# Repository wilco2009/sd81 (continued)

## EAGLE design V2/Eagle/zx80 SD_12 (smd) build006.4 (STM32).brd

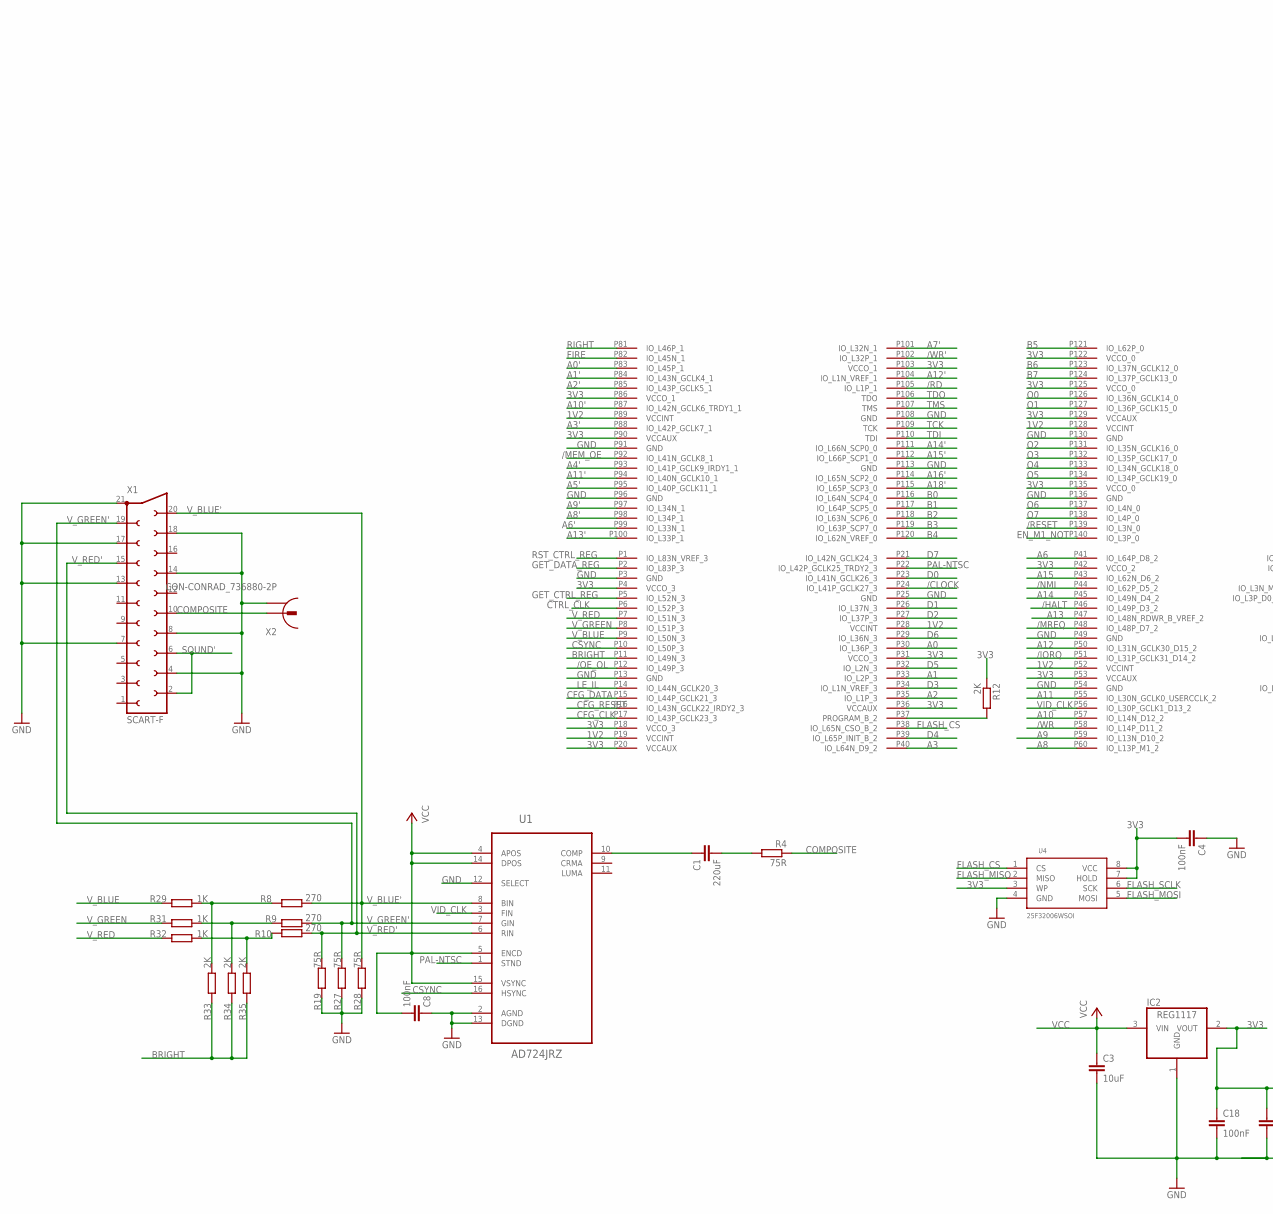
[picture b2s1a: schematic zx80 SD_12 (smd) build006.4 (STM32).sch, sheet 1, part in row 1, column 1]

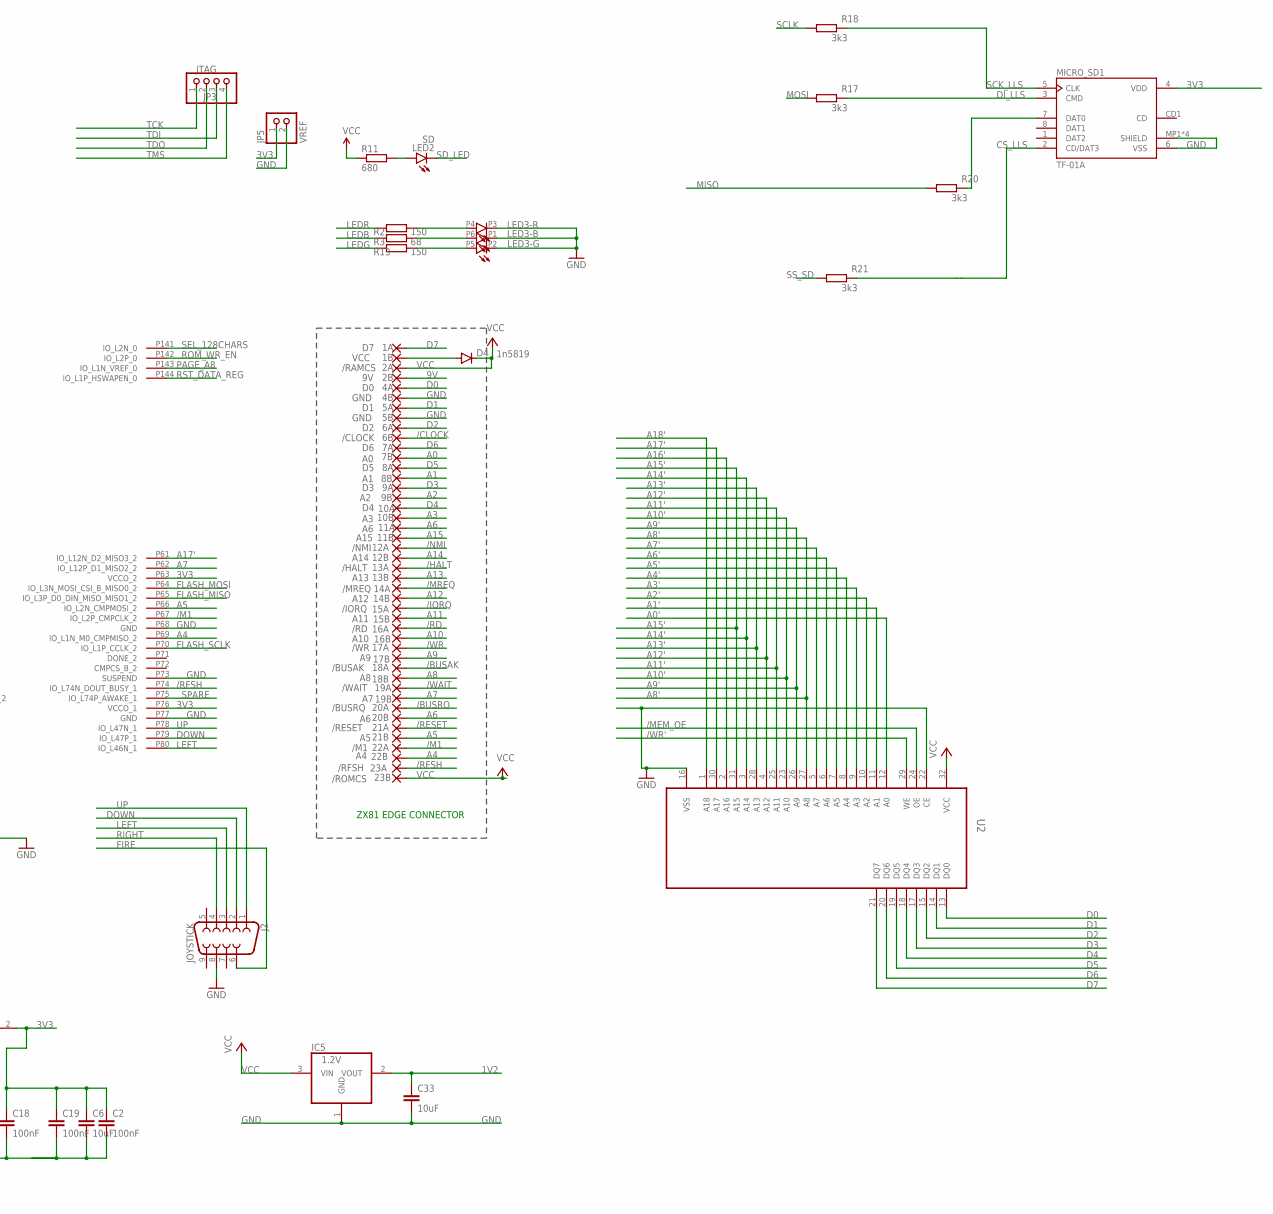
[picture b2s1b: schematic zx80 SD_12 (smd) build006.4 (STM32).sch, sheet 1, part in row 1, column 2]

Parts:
1A: D7; EDGEPIN
1B: VCC; EDGEPIN
2A: /RAMCS; EDGEPIN
2B: 9V; EDGEPIN
4A: D0; EDGEPIN
4B, 5B: GND; EDGEPIN
5A: D1; EDGEPIN
6A: D2; EDGEPIN
6B: /CLOCK; EDGEPIN
7A: D6; EDGEPIN
7B: A0; EDGEPIN
8A: D5; EDGEPIN
8B: A1; EDGEPIN
9A: D3; EDGEPIN
9B: A2; EDGEPIN
10A: D4; EDGEPIN
10B: A3; EDGEPIN
11A, 20B: A6; EDGEPIN
11B: A15; EDGEPIN
12A: /NMI; EDGEPIN
12B: A14; EDGEPIN
13A: /HALT; EDGEPIN
13B: A13; EDGEPIN
14A: /MREQ; EDGEPIN
14B: A12; EDGEPIN
15A: /IORQ; EDGEPIN
15B: A11; EDGEPIN
16A: /RD; EDGEPIN
16B: A10; EDGEPIN
17A: /WR; EDGEPIN
17B: A9; EDGEPIN
18A: /BUSAK; EDGEPIN
18B: A8; EDGEPIN
19A: /WAIT; EDGEPIN
19B: A7; EDGEPIN
20A: /BUSRQ; EDGEPIN
21A: /RESET; EDGEPIN
21B: A5; EDGEPIN
22A: /M1; EDGEPIN
22B: A4; EDGEPIN
23A: /RFSH; EDGEPIN
23B: /ROMCS; EDGEPIN
C1: 220uF; C0603K
C2, C4, C18, C19: 100nF; C0603
C3, C6, C33: 10uF; C0603
C8: 100nF; C0603K
D4: 1n5819; SOD323-W
IC2: REG1117; SOT223
IC5: 1.2V; SOT223
J2: JOYSTICK; DB9_MALE
JP3: JTAG; 1X04
JP5: VREF; 1X02
LED2: SD; CHIPLED_0805
LED3: STATUS; 3535-PLCC6
MICRO_SD1: TF-01A
R2, R13: 150; R0603
R3: 68; R0603
R4: 75R; R0603
R8, R9, R10: 270; R0402
R11: 680; R0603
R12: 2K; R0603
R17, R18, R20, R21: 3k3; R0603
R19, R27, R28: 75R; R0402
R29, R31, R32: 1K; R0402
R33, R34, R35: 2K; R0402
U1: AD724JRZ; SOIC127P1032X265-16N
U2: AS6C4008; SOP32-5
U4: 25F32006WSOI; SO08-EIAJ
U$1: XC6SLX9-2TQG144C; TQ144
X1: SCART-F
X2: CON-CONRAD_736880-2P; 3P

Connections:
1V2: C33.1, IC5.2 (VOUT), U$1.P19 (VCCINT), U$1.P28 (VCCINT), U$1.P52 (VCCINT), U$1.P89 (VCCINT), U$1.P128 (VCCINT)
3V3: C2.1, C4.2, C6.1, C18.1, C19.1, IC2.2 (VOUT), JP5.1, MICRO_SD1.4 (VDD), R12.1, U4.3 (WP), U4.7 (HOLD), U4.8 (VCC), U$1.P4 (VCCO_3), U$1.P18 (VCCO_3), U$1.P20 (VCCAUX), U$1.P31 (VCCO_3), U$1.P36 (VCCAUX), U$1.P42 (VCCO_2), U$1.P53 (VCCAUX), U$1.P63 (VCCO_2), U$1.P76 (VCCO_1), U$1.P86 (VCCO_1), U$1.P90 (VCCAUX), U$1.P103 (VCCO_1), U$1.P122 (VCCO_0), U$1.P125 (VCCO_0), U$1.P129 (VCCAUX), U$1.P135 (VCCO_0); also elsewhere on the board
9V: 2B.1
/BUSAK: 18A.1
/BUSRQ: 20A.1
/CLOCK: 6B.1, U$1.P24 (IO_L41P_GCLK27_3)
/HALT: 13A.1, U$1.P46 (IO_L49P_D3_2)
/IORQ: 15A.1, U$1.P51 (IO_L31P_GCLK31_D14_2)
/M1: 22A.1, U$1.P67 (IO_L2P_CMPCLK_2)
/MEM_OE: U2.24 (OE), U$1.P92 (IO_L41N_GCLK8_1)
/MREQ: 14A.1, U$1.P48 (IO_L48P_D7_2)
/NMI: 12A.1, U$1.P44 (IO_L62P_D5_2)
/OE_OL: U$1.P12 (IO_L49P_3); also elsewhere on the board
/RD: 16A.1, U$1.P105 (IO_L1P_1)
/RESET: 21A.1, U$1.P139 (IO_L3N_0); also elsewhere on the board
/RFSH: 23A.1, U$1.P74 (IO_L74N_DOUT_BUSY_1)
/WAIT: 19A.1; also elsewhere on the board
/WR: 17A.1, U$1.P58 (IO_L14P_D11_2)
/WR': U2.29 (WE), U$1.P102 (IO_L32P_1); also elsewhere on the board
A0: 7B.1, U$1.P30 (IO_L36P_3)
A0': U2.12 (A0), U$1.P83 (IO_L45P_1); also elsewhere on the board
A1: 8B.1, U$1.P33 (IO_L2P_3)
A1': U2.11 (A1), U$1.P84 (IO_L43N_GCLK4_1); also elsewhere on the board
A2: 9B.1, U$1.P35 (IO_L1P_3)
A2': U2.10 (A2), U$1.P85 (IO_L43P_GCLK5_1); also elsewhere on the board
A3: 10B.1, U$1.P40 (IO_L64N_D9_2)
A3': U2.9 (A3), U$1.P88 (IO_L42P_GCLK7_1); also elsewhere on the board
A4: 22B.1, U$1.P69 (IO_L1N_M0_CMPMISO_2)
A4': U2.8 (A4), U$1.P93 (IO_L41P_GCLK9_IRDY1_1); also elsewhere on the board
A5: 21B.1, U$1.P66 (IO_L2N_CMPMOSI_2)
A5': U2.7 (A5), U$1.P95 (IO_L40P_GCLK11_1); also elsewhere on the board
A6: 11A.1, 20B.1, U$1.P41 (IO_L64P_D8_2)
A6': U2.6 (A6), U$1.P99 (IO_L33N_1); also elsewhere on the board
A7: 19B.1, U$1.P62 (IO_L12P_D1_MISO2_2)
A7': U2.5 (A7), U$1.P101 (IO_L32N_1); also elsewhere on the board
A8: 18B.1, U$1.P60 (IO_L13P_M1_2)
A8': U2.27 (A8), U$1.P98 (IO_L34P_1); also elsewhere on the board
A9: 17B.1, U$1.P59 (IO_L13N_D10_2)
A9': U2.26 (A9), U$1.P97 (IO_L34N_1); also elsewhere on the board
A10: 16B.1, U$1.P57 (IO_L14N_D12_2)
A10': U2.23 (A10), U$1.P87 (IO_L42N_GCLK6_TRDY1_1); also elsewhere on the board
A11: 15B.1, U$1.P55 (IO_L30N_GCLK0_USERCCLK_2)
A11': U2.25 (A11), U$1.P94 (IO_L40N_GCLK10_1); also elsewhere on the board
A12: 14B.1, U$1.P50 (IO_L31N_GCLK30_D15_2)
A12': U2.4 (A12), U$1.P104 (IO_L1N_VREF_1); also elsewhere on the board
A13: 13B.1, U$1.P47 (IO_L48N_RDWR_B_VREF_2)
A13': U2.28 (A13), U$1.P100 (IO_L33P_1); also elsewhere on the board
A14: 12B.1, U$1.P45 (IO_L49N_D4_2)
A14': U2.3 (A14), U$1.P111 (IO_L66N_SCP0_0); also elsewhere on the board
A15: 11B.1, U$1.P43 (IO_L62N_D6_2)
A15': U2.31 (A15), U$1.P112 (IO_L66P_SCP1_0); also elsewhere on the board
A16': U2.2 (A16), U$1.P114 (IO_L65N_SCP2_0); also elsewhere on the board
A17': U2.30 (A17), U$1.P61 (IO_L12N_D2_MISO3_2); also elsewhere on the board
A18': U2.1 (A18), U$1.P115 (IO_L65P_SCP3_0); also elsewhere on the board
B0: U$1.P116 (IO_L64N_SCP4_0); also elsewhere on the board
B1: U$1.P117 (IO_L64P_SCP5_0); also elsewhere on the board
B2: U$1.P118 (IO_L63N_SCP6_0); also elsewhere on the board
B3: U$1.P119 (IO_L63P_SCP7_0); also elsewhere on the board
B4: U$1.P120 (IO_L62N_VREF_0); also elsewhere on the board
B5: U$1.P121 (IO_L62P_0); also elsewhere on the board
B6: U$1.P123 (IO_L37N_GCLK12_0); also elsewhere on the board
B7: U$1.P124 (IO_L37P_GCLK13_0); also elsewhere on the board
BRIGHT: R33.1, R34.1, R35.1, U$1.P11 (IO_L49N_3)
CFG_CLK: U$1.P17 (IO_L43P_GCLK23_3); also elsewhere on the board
CFG_DATA: U$1.P15 (IO_L44P_GCLK21_3); also elsewhere on the board
CFG_RESET: U$1.P16 (IO_L43N_GCLK22_IRDY2_3); also elsewhere on the board
COMPOSITE: R4.1, X1.10, X2.2 (1)
CSYNC: U1.16 (HSYNC), U$1.P10 (IO_L50P_3)
CS_LLS: MICRO_SD1.2 (CD/DAT3), R21.2
CTRL_CLK: U$1.P6 (IO_L52P_3); also elsewhere on the board
D0: 4A.1, U2.13 (DQ0), U$1.P23 (IO_L41N_GCLK26_3)
D1: 5A.1, U2.14 (DQ1), U$1.P26 (IO_L37N_3)
D2: 6A.1, U2.15 (DQ2), U$1.P27 (IO_L37P_3)
D3: 9A.1, U2.17 (DQ3), U$1.P34 (IO_L1N_VREF_3)
D4: 10A.1, U2.18 (DQ4), U$1.P39 (IO_L65P_INIT_B_2)
D5: 8A.1, U2.19 (DQ5), U$1.P32 (IO_L2N_3)
D6: 7A.1, U2.20 (DQ6), U$1.P29 (IO_L36N_3)
D7: 1A.1, U2.21 (DQ7), U$1.P21 (IO_L42N_GCLK24_3)
DI_LLS: MICRO_SD1.3 (CMD), R17.2
DOWN: J2.2, U$1.P79 (IO_L47P_1)
EN_M1_NOT: U$1.P140 (IO_L3P_0); also elsewhere on the board
FIRE: J2.6, U$1.P82 (IO_L45N_1)
FLASH_CS: U4.1 (CS), U$1.P38 (IO_L65N_CSO_B_2)
FLASH_MISO: U4.2 (MISO), U$1.P65 (IO_L3P_D0_DIN_MISO_MISO1_2)
FLASH_MOSI: U4.5 (MOSI), U$1.P64 (IO_L3N_MOSI_CSI_B_MISO0_2)
FLASH_SCLK: U4.6 (SCK), U$1.P70 (IO_L1P_CCLK_2)
GET_CTRL_REG: U$1.P5 (IO_L52N_3); also elsewhere on the board
GET_DATA_REG: U$1.P2 (IO_L83P_3); also elsewhere on the board
GND: 4B.1, 5B.1, C2.2, C3.2, C4.1, C6.2, C8.1, C18.2, C19.2, C33.2, IC2.1 (GND), IC5.1 (GND), J2.8, JP5.2, LED3.P1 (C), LED3.P2 (C), LED3.P3 (C), MICRO_SD1.6 (VSS), MICRO_SD1.MP1 (SHIELD), MICRO_SD1.MP2 (SHIELD), MICRO_SD1.MP3 (SHIELD), MICRO_SD1.MP4 (SHIELD), R19.2, R27.2, R28.2, U1.2 (AGND), U1.12 (SELECT), U1.13 (DGND), U2.16 (VSS), U2.22 (CE), U4.4 (GND), U$1.P3 (GND), U$1.P13 (GND), U$1.P25 (GND), U$1.P49 (GND), U$1.P54 (GND), U$1.P68 (GND), U$1.P73 (SUSPEND), U$1.P77 (GND), U$1.P91 (GND), U$1.P96 (GND), U$1.P108 (GND), U$1.P113 (GND), U$1.P130 (GND), U$1.P136 (GND), X1.4, X1.7, X1.8, X1.13, X1.14, X1.17, X1.18, X1.21, X2.1 (2); also elsewhere on the board
LEDB: R3.1; also elsewhere on the board
LEDG: R13.1; also elsewhere on the board
LEDR: R2.1; also elsewhere on the board
LEFT: J2.3, U$1.P80 (IO_L46N_1)
LE_IL: U$1.P14 (IO_L44N_GCLK20_3); also elsewhere on the board
MISO: R20.1; also elsewhere on the board
MOSI: R17.1; also elsewhere on the board
unnamed: C1.1, U1.10 (COMP)
unnamed: MICRO_SD1.7 (DAT0), R20.2
unnamed: 1B.1, D4.A
unnamed: C1.2, R4.2
unnamed: R12.2, U$1.P37 (PROGRAM_B_2)
unnamed: LED2.A, R11.2
unnamed: LED3.P4 (A), R2.2
unnamed: LED3.P6 (A), R3.2
unnamed: LED3.P5 (A), R13.2
unnamed: R8.2, R29.2, R33.2
unnamed: R9.2, R31.2, R34.2
unnamed: R10.2, R32.2, R35.2
O0: U$1.P126 (IO_L36N_GCLK14_0); also elsewhere on the board
O1: U$1.P127 (IO_L36P_GCLK15_0); also elsewhere on the board
O2: U$1.P131 (IO_L35N_GCLK16_0); also elsewhere on the board
O3: U$1.P132 (IO_L35P_GCLK17_0); also elsewhere on the board
O4: U$1.P133 (IO_L34N_GCLK18_0); also elsewhere on the board
O5: U$1.P134 (IO_L34P_GCLK19_0); also elsewhere on the board
O6: U$1.P137 (IO_L4N_0); also elsewhere on the board
O7: U$1.P138 (IO_L4P_0); also elsewhere on the board
PAGE_A8: U$1.P143 (IO_L1N_VREF_0); also elsewhere on the board
PAL-NTSC: U1.1 (STND), U$1.P22 (IO_L42P_GCLK25_TRDY2_3)
RIGHT: J2.4, U$1.P81 (IO_L46P_1)
ROM_WR_EN: U$1.P142 (IO_L2P_0); also elsewhere on the board
RST_CTRL_REG: U$1.P1 (IO_L83N_VREF_3); also elsewhere on the board
RST_DATA_REG: U$1.P144 (IO_L1P_HSWAPEN_0); also elsewhere on the board
SCK_LLS: MICRO_SD1.5 (CLK), R18.2
SCLK: R18.1; also elsewhere on the board
SD_LED: LED2.C; also elsewhere on the board
SEL_128CHARS: U$1.P141 (IO_L2N_0); also elsewhere on the board
SOUND': X1.2, X1.6; also elsewhere on the board
SPARE: U$1.P75 (IO_L74P_AWAKE_1)
SS_SD: R21.1; also elsewhere on the board
TCK: JP3.1, U$1.P109 (TCK)
TDI: JP3.3, U$1.P110 (TDI)
TDO: JP3.2, U$1.P106 (TDO)
TMS: JP3.4, U$1.P107 (TMS)
UP: J2.1, U$1.P78 (IO_L47N_1)
VCC: 2A.1, 23B.1, C3.1, C8.2, D4.C, IC2.3 (VIN), IC5.3 (VIN), R11.1, U1.4 (APOS), U1.5 (ENCD), U1.14 (DPOS), U1.15 (VSYNC), U2.32 (VCC); also elsewhere on the board
VID_CLK: U1.3 (FIN), U$1.P56 (IO_L30P_GCLK1_D13_2)
V_BLUE: R29.1, U$1.P9 (IO_L50N_3)
V_BLUE': R8.1, R28.1, U1.8 (BIN), X1.20
V_GREEN: R31.1, U$1.P8 (IO_L51P_3)
V_GREEN': R9.1, R27.1, U1.7 (GIN), X1.19
V_RED: R32.1, U$1.P7 (IO_L51N_3)
V_RED': R10.1, R19.1, U1.6 (RIN), X1.15

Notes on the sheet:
ZX81 EDGE CONNECTOR

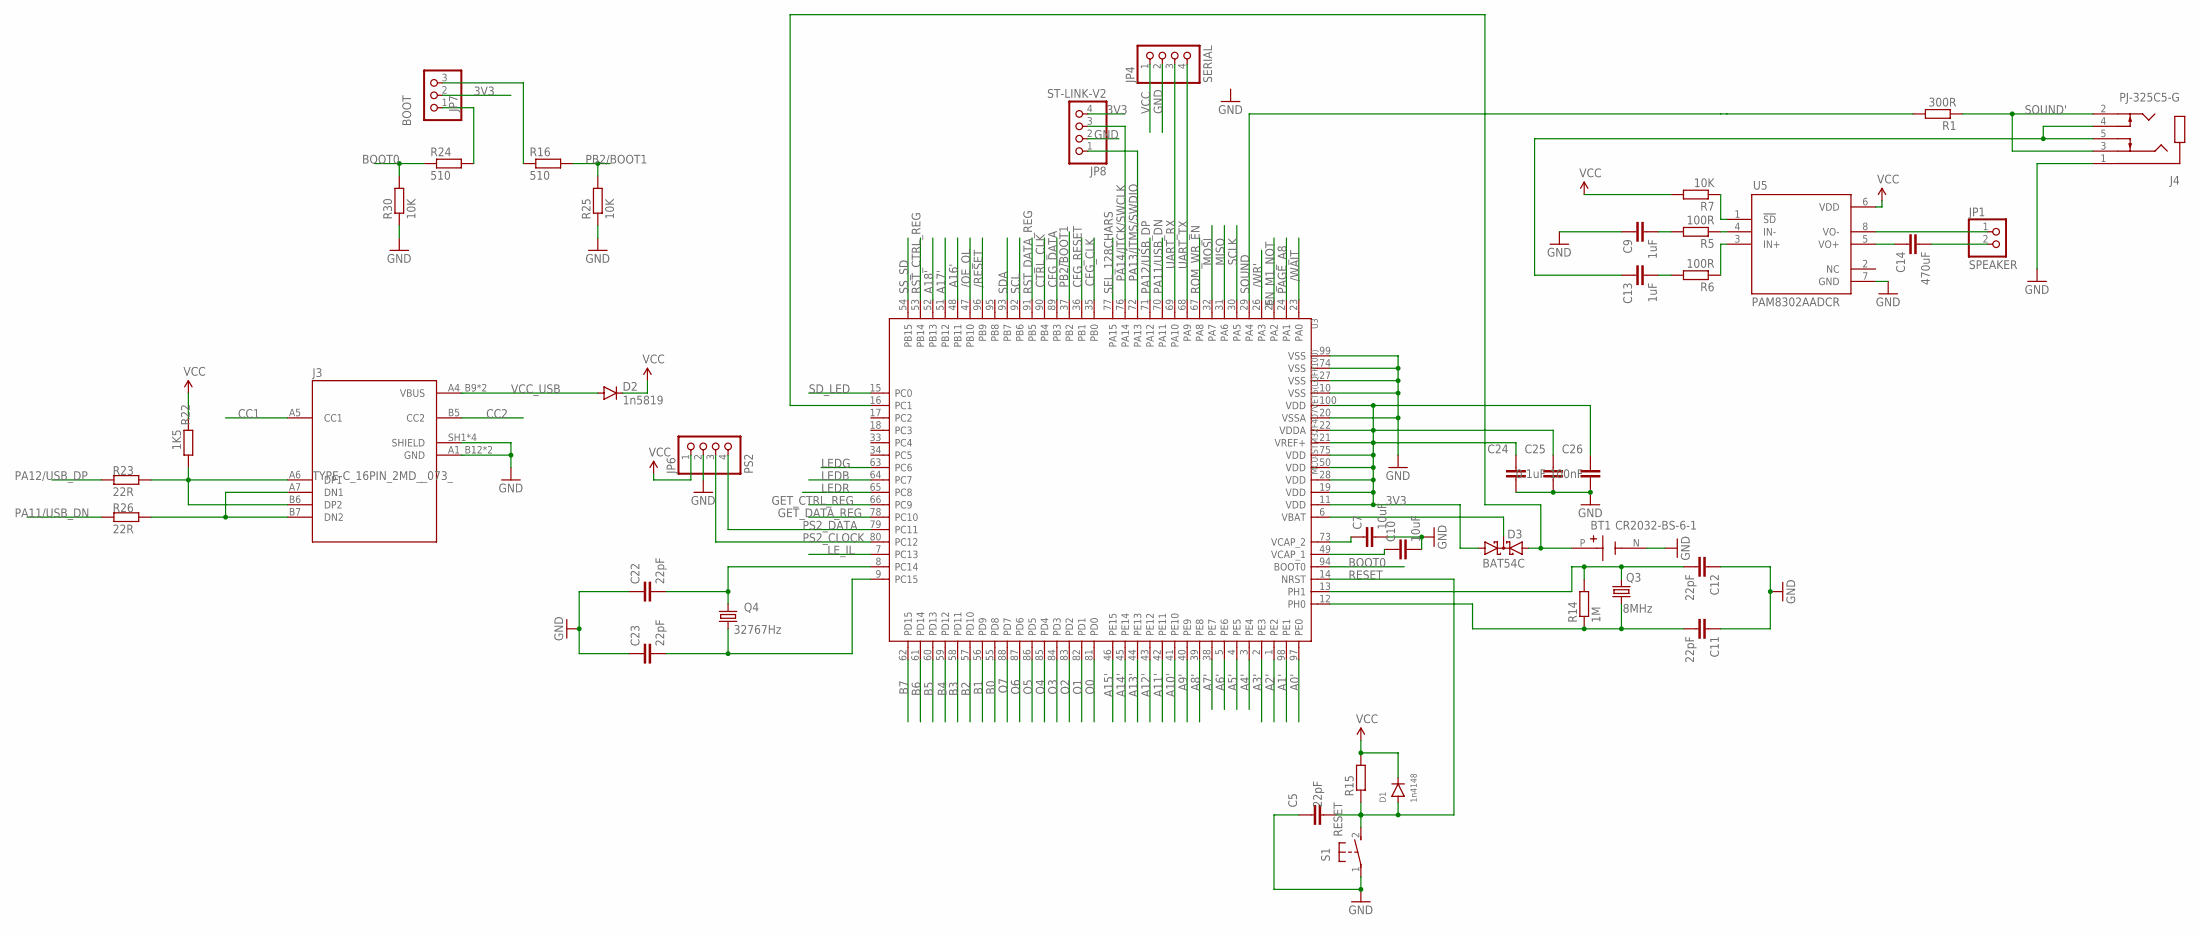
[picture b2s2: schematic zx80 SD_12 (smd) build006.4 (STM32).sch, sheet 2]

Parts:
BT1: CR2032-BS-6-1; BAT_CR2032-BS-6-1
C5, C11, C12, C22, C23: 22pF; C0603
C7, C10: 10uF; C1206
C9, C13: 1uF; C0603
C14: 470uF; C0603
C24, C25: 0.1uF; C0603
C26: 100nF; C0603
D1: 1n4148; SOD123
D2: 1n5819; SOD323-W
D3: BAT54C; SOT23
J3: TYPE-C_16PIN_2MD__073_; SHOUHAN_TYPE-C_16PIN_2MD__073_
J4: PJ-325C5-G; XKB_PJ-325C5-G
JP1: SPEAKER; 1X02
JP4: SERIAL; 1X04
JP6: PS2; 1X04
JP7: BOOT; 1X03
JP8: ST-LINK-V2; 1X04
Q3: 8MHz; 3.2X2.5_KX-7
Q4: 32767Hz; 3.2X1.5
R1: 300R; R0603
R5, R6: 100R; R0603
R7, R25, R30: 10K; R0603
R14: 1M; R0603
R15: 3K3; R0603
R16, R24: 510; R0603
R22: 1K5; R0603
R23, R26: 22R; R0603
S1: RESET; B3F-31XX
U3: MCU-STM32F407VET6(LQFP100); LQFP100-0.5-13.8X13.8MM
U5: PAM8302AADCR; SOIC127P600X170-8N

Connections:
3V3: C24.1, C25.1, C26.1, D3.1 (A1), JP7.2, JP8.4, U3.11 (VDD), U3.19 (VDD), U3.21 (VREF+), U3.22 (VDDA), U3.28 (VDD), U3.50 (VDD), U3.75 (VDD), U3.100 (VDD); also elsewhere on the board
/OE_OL: U3.47 (PB10); also elsewhere on the board
/RESET: U3.96 (PB9); also elsewhere on the board
/WAIT: U3.23 (PA0); also elsewhere on the board
/WR': U3.26 (PA3); also elsewhere on the board
A0': U3.97 (PE0); also elsewhere on the board
A1': U3.98 (PE1); also elsewhere on the board
A2': U3.1 (PE2); also elsewhere on the board
A3': U3.2 (PE3); also elsewhere on the board
A4': U3.3 (PE4); also elsewhere on the board
A5': U3.4 (PE5); also elsewhere on the board
A6': U3.5 (PE6); also elsewhere on the board
A7': U3.38 (PE7); also elsewhere on the board
A8': U3.39 (PE8); also elsewhere on the board
A9': U3.40 (PE9); also elsewhere on the board
A10': U3.41 (PE10); also elsewhere on the board
A11': U3.42 (PE11); also elsewhere on the board
A12': U3.43 (PE12); also elsewhere on the board
A13': U3.44 (PE13); also elsewhere on the board
A14': U3.45 (PE14); also elsewhere on the board
A15': U3.46 (PE15); also elsewhere on the board
A16': U3.48 (PB11); also elsewhere on the board
A17': U3.51 (PB12); also elsewhere on the board
A18': U3.52 (PB13); also elsewhere on the board
B0: U3.55 (PD8); also elsewhere on the board
B1: U3.56 (PD9); also elsewhere on the board
B2: U3.57 (PD10); also elsewhere on the board
B3: U3.58 (PD11); also elsewhere on the board
B4: U3.59 (PD12); also elsewhere on the board
B5: U3.60 (PD13); also elsewhere on the board
B6: U3.61 (PD14); also elsewhere on the board
B7: U3.62 (PD15); also elsewhere on the board
BAT: BT1.P (POS), D3.2 (A2), U3.16 (PC1)
BOOT0: R24.1, R30.2, U3.94 (BOOT0)
CC1: J3.A5 (CC1)
CC2: J3.B5 (CC2)
CFG_CLK: U3.35 (PB0); also elsewhere on the board
CFG_DATA: U3.89 (PB3); also elsewhere on the board
CFG_RESET: U3.36 (PB1); also elsewhere on the board
CTRL_CLK: U3.90 (PB4); also elsewhere on the board
EN_M1_NOT: U3.25 (PA2); also elsewhere on the board
GET_CTRL_REG: U3.66 (PC9); also elsewhere on the board
GET_DATA_REG: U3.78 (PC10); also elsewhere on the board
GND: BT1.N (NEG), C5.1, C7.2, C9.1, C10.2, C11.1, C12.1, C22.1, C23.1, C24.2, C25.2, C26.2, J3.A1_B12 (GND), J3.B1_A12 (GND), J3.SH1 (SHIELD), J3.SH2 (SHIELD), J3.SH3 (SHIELD), J3.SH4 (SHIELD), J4.1, JP4.2, JP6.2, JP8.2, R25.1, R30.1, S1.1, U3.10 (VSS), U3.20 (VSSA), U3.27 (VSS), U3.74 (VSS), U3.99 (VSS), U5.7 (GND); also elsewhere on the board
LEDB: U3.64 (PC7); also elsewhere on the board
LEDG: U3.63 (PC6); also elsewhere on the board
LEDR: U3.65 (PC8); also elsewhere on the board
LE_IL: U3.7 (PC13); also elsewhere on the board
MISO: U3.31 (PA6); also elsewhere on the board
MOSI: U3.32 (PA7); also elsewhere on the board
unnamed: J3.A6 (DP1), J3.B6 (DP2), R22.1, R23.1
unnamed: D3.3 (CC), U3.6 (VBAT)
unnamed: R6.1, U5.3 (IN+)
unnamed: R5.1, U5.4 (IN-)
unnamed: R7.1, U5.1 (!SD)
unnamed: C7.1, U3.73 (VCAP_2)
unnamed: J3.A7 (DN1), J3.B7 (DN2), R26.1
unnamed: C9.2, R5.2
unnamed: C13.2, R6.2
unnamed: C10.1, U3.49 (VCAP_1)
unnamed: C11.2, Q3.1, R14.1, U3.12 (PH0)
unnamed: C12.2, Q3.3 (2), R14.2, U3.13 (PH1)
unnamed: JP7.3, R16.1
unnamed: JP7.1, R24.2
unnamed: C22.2, Q4.2, U3.8 (PC14)
unnamed: C23.2, Q4.1, U3.9 (PC15)
unnamed: C14.1, U5.5 (VO+)
unnamed: JP1.1, U5.8 (VO-)
unnamed: C13.1, J4.4, J4.5
unnamed: C14.2, JP1.2
O0: U3.81 (PD0); also elsewhere on the board
O1: U3.82 (PD1); also elsewhere on the board
O2: U3.83 (PD2); also elsewhere on the board
O3: U3.84 (PD3); also elsewhere on the board
O4: U3.85 (PD4); also elsewhere on the board
O5: U3.86 (PD5); also elsewhere on the board
O6: U3.87 (PD6); also elsewhere on the board
O7: U3.88 (PD7); also elsewhere on the board
PA11/USB_DN: R26.2, U3.70 (PA11)
PA12/USB_DP: R23.2, U3.71 (PA12)
PA13/JTMS/SWDIO: JP8.1, U3.72 (PA13)
PA14/JTCK/SWCLK: JP8.3, U3.76 (PA14)
PAGE_A8: U3.24 (PA1); also elsewhere on the board
PB2/BOOT1: R16.2, R25.2, U3.37 (PB2)
PS2_CLOCK: JP6.3, U3.80 (PC12)
PS2_DATA: JP6.4, U3.79 (PC11)
RESET: C5.2, D1.A, R15.1, S1.2 (S), U3.14 (NRST)
ROM_WR_EN: U3.67 (PA8); also elsewhere on the board
RST_CTRL_REG: U3.53 (PB14); also elsewhere on the board
RST_DATA_REG: U3.91 (PB5); also elsewhere on the board
SCL: U3.92 (PB6)
SCLK: U3.30 (PA5); also elsewhere on the board
SDA: U3.93 (PB7)
SD_LED: U3.15 (PC0); also elsewhere on the board
SEL_128CHARS: U3.77 (PA15); also elsewhere on the board
SOUND: R1.2, U3.29 (PA4)
SOUND': J4.2, J4.3, R1.1; also elsewhere on the board
SS_SD: U3.54 (PB15); also elsewhere on the board
UART_RX: JP4.3, U3.69 (PA10)
UART_TX: JP4.4, U3.68 (PA9)
VCC: D1.C, D2.C, JP4.1, JP6.1, R7.2, R15.2, R22.2, U5.6 (VDD); also elsewhere on the board
VCC_USB: D2.A, J3.A4_B9 (VBUS), J3.B4_A9 (VBUS)

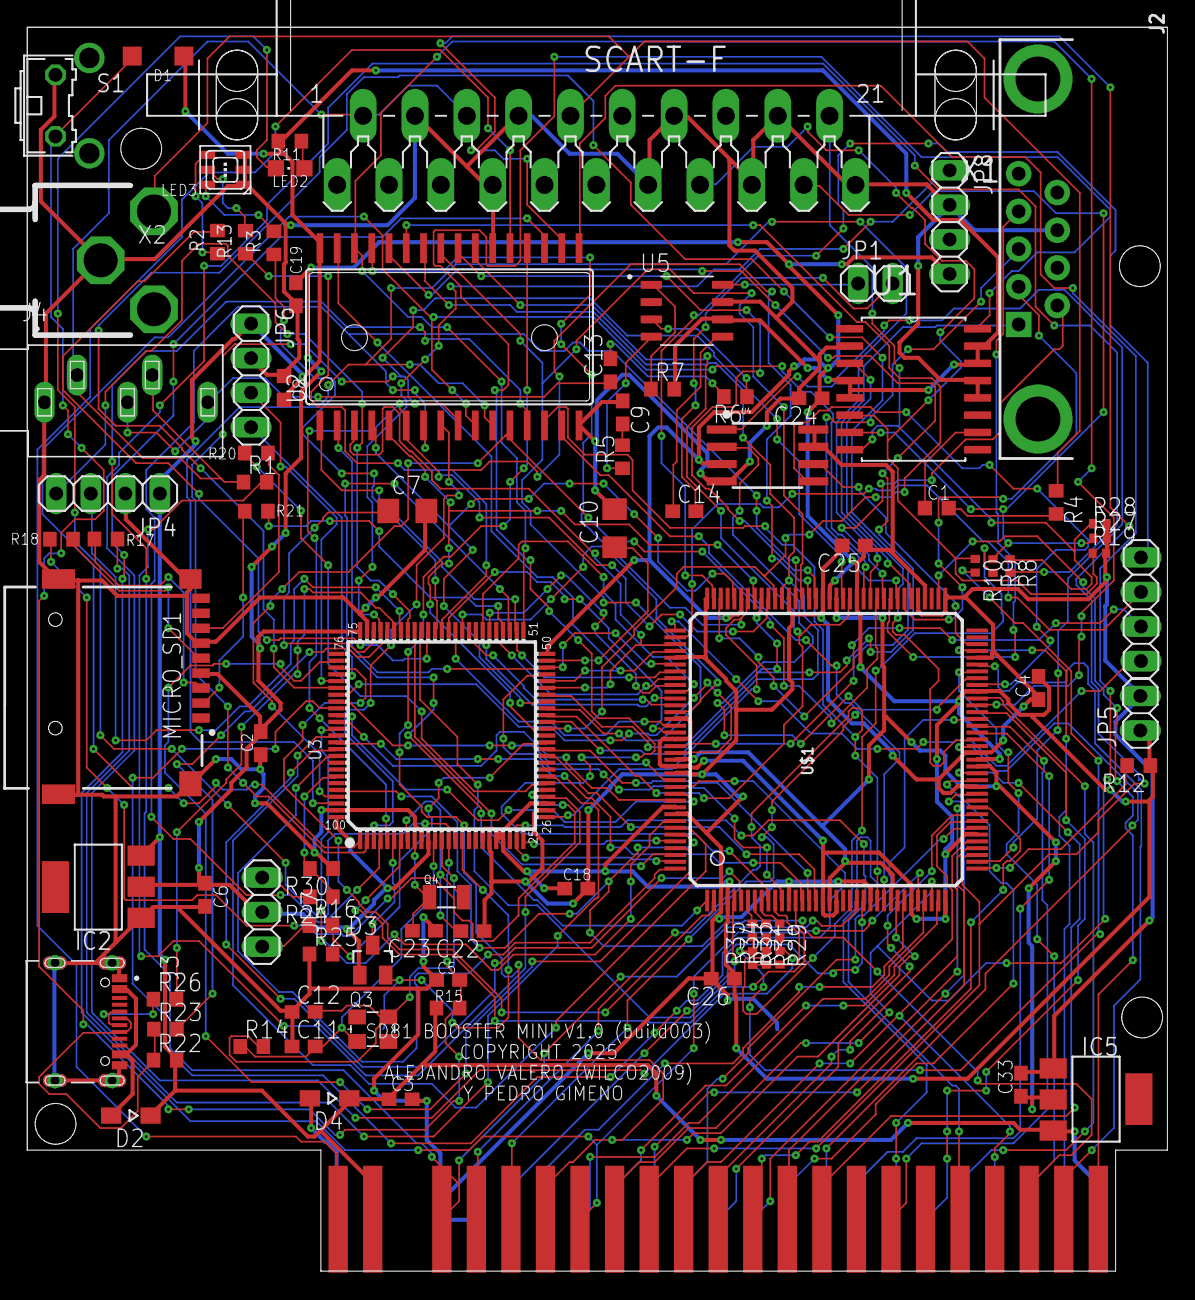
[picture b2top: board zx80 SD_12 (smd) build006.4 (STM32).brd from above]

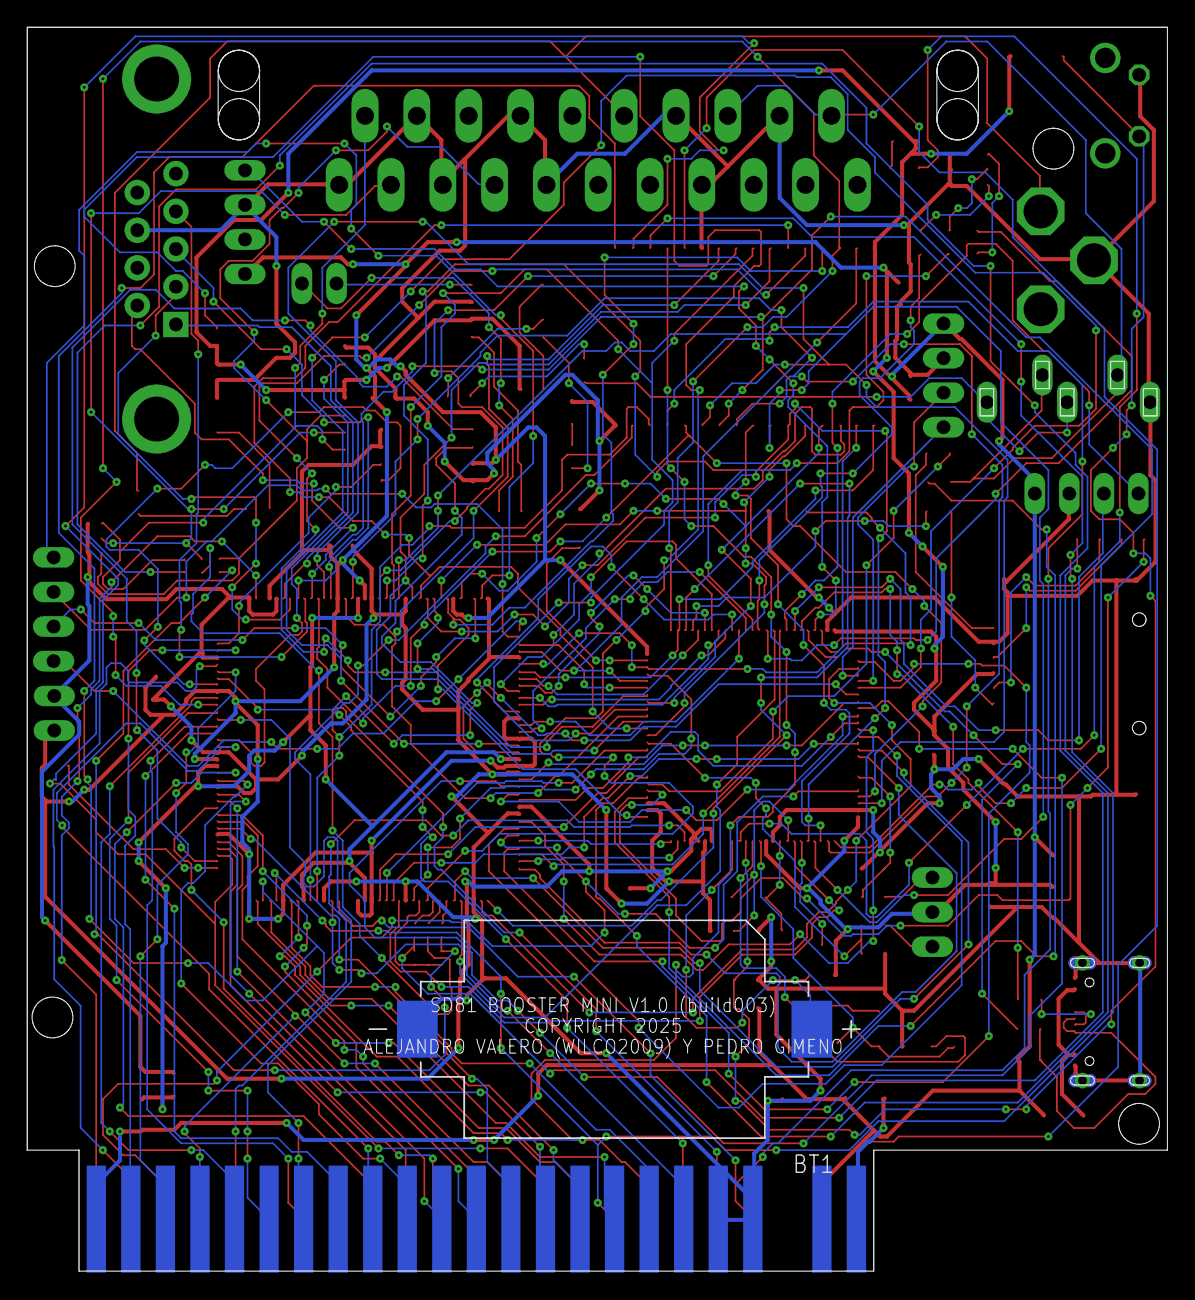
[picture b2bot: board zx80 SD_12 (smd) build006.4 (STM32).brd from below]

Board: 2 copper layers, 83.8 x 91.4 mm, 132 parts (23 on the bottom side), 172 nets.

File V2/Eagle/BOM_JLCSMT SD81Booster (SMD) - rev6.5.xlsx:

Comment | Designator | Footprint | JLCPCB Part #（optional）
220uF | C1 | SMD,D6.3xL7.7mm | C32514
100nF | C2 | C0603 | C14663
10uF | C3 | C0603 | C19702
100nF | C4 | C0603 | C14663
22pF | C5 | C0603 | C1653
10uF | C6 | C0603 | C19702
10uF | C7 | C0603 | C19702
100nF | C8 | C0603 | C14663
1uF | C9 | C0603 | C15849
10uF | C10 | C0603 | C19702
22pF | C11 | C0603 | C1653
22pF | C12 | C0603 | C1653
1uF | C13 | C0603 | C15849
470uF | C14 | SMD,D6.3xL7.7mm | C3354
100nF | C18 | C0603 | C14663
100nF | C19 | C0603 | C14663
22pF | C22 | C0603 | C1653
22pF | C23 | C0603 | C1653
100nF | C24 | C0603 | C14663
100nF | C25 | C0603 | C14663
100nF | C26 | C0603 | C14663
10uF | C33 | C0603 | C19702
1n4148 | D1 | SOD123 | C81598
1n5819 | D2 | SOD323-W | C191023
BAT54C | D3 | SOT23 | C22466350
1n5819 | D4 | SOD323-W | C191023
REG1117 | IC2 | SOT223 | C6186
1,2V | IC5 | SOT223 | C347218
JOYSTICK | J2 | DR9_MALE | C3020655
TYPE-C_16PIN_2MD__073_ | J3 | SHOUHAN_TYPE-C_16PIN_2MD__073_ | C393939
PJ-325C5-G | J4 | XKB_PJ-325C5-G | C2884942
PINH 1x02 | JP1 | 1X02 | C492401
PINH 1x02 | JP2 | 1X02 | C492401
PINH 1x04 | JP3 | 1X04
PINH 1x04 | JP4 | 1X04 | C2691448
PINH 1x02 | JP5 | 1X02
PINH 1x04 | JP6 | 1X04 | C2691448
PINH 1x03 | JP7 | 1X03 | C2937625
PINH 1x04 | JP8 | 1X04 | C2691448
SD | LED2 | CHIPLED_0805 | C2297
STATUS | LED3 | 3535-PLCC6 | C110402
TF-01A | MICRO_SD1 | TF-01A | C22383473
8MHz | Q3 | 3,2X2,5_KX-7 | C403948
32767Hz | Q4 | 3,2X1,5 | C32346
300R | R1 | R0603 | C23025
150 | R2 | R0603 | C22808
68 | R3 | R0603 | C27592
75R | R4 | R0603 | C4275
100R | R5 | R0603 | C22775
100R | R6 | R0603 | C22775
10K | R7 | R0603 | C25804
270 | R8 | R0603 | C22966
270 | R9 | R0603 | C22966
270 | R10 | R0603 | C22966
680 | R11 | R0603 | C23228
2K | R12 | R0402 | C4109
150 | R13 | R0603 | C22808
1M | R14 | R0603 | C409676
3k3 | R15 | R0603 | C22978
510 | R16 | R0603 | C23193
3k3 | R17 | R0603 | C22978
3k3 | R18 | R0603 | C22978
75R | R19 | R0603 | C4275
3k3 | R20 | R0603 | C22978
3k3 | R21 | R0603 | C22978
1K5 | R22 | R0603 | C22843
22R | R23 | R0603 | C23345
510 | R24 | R0603 | C23193
10K | R25 | R0603 | C25804
22R | R26 | R0603 | C23345
75R | R27 | R0603 | C4275
75R | R28 | R0603 | C4275
1K | R29 | R0402 | C11702
10K | R30 | R0603 | C25804
1K | R31 | R0402 | C11702
1K | R32 | R0402 | C11702
2K | R33 | R0402 | C4109
2K | R34 | R0402 | C4109
2K | R35 | R0402 | C4109
100R | R36 | R0603 | C22775
RESET | S1 | B3F-31XX | C231320
AD724 | U1 | SOIC127P1032X265-16N
AS6C4008 | U2 | SOP32-5 | C2952831
MCU-STM32F407VET6(LQFP100) | U3 | LQFP100-0,5-13,8X13,8MM | C28730
W25Q128JVSIQ | U4 | SO08-EIAJ | C97521
PAM8302 | U5 | SOIC127P600X170-8N | C112137
XC6SLX9-2TQG144C | U6 | TQ144 | C27408
SCART-F | X1 | SCART-F
CON-CONRAD_736880-2P | X2 | 3P
